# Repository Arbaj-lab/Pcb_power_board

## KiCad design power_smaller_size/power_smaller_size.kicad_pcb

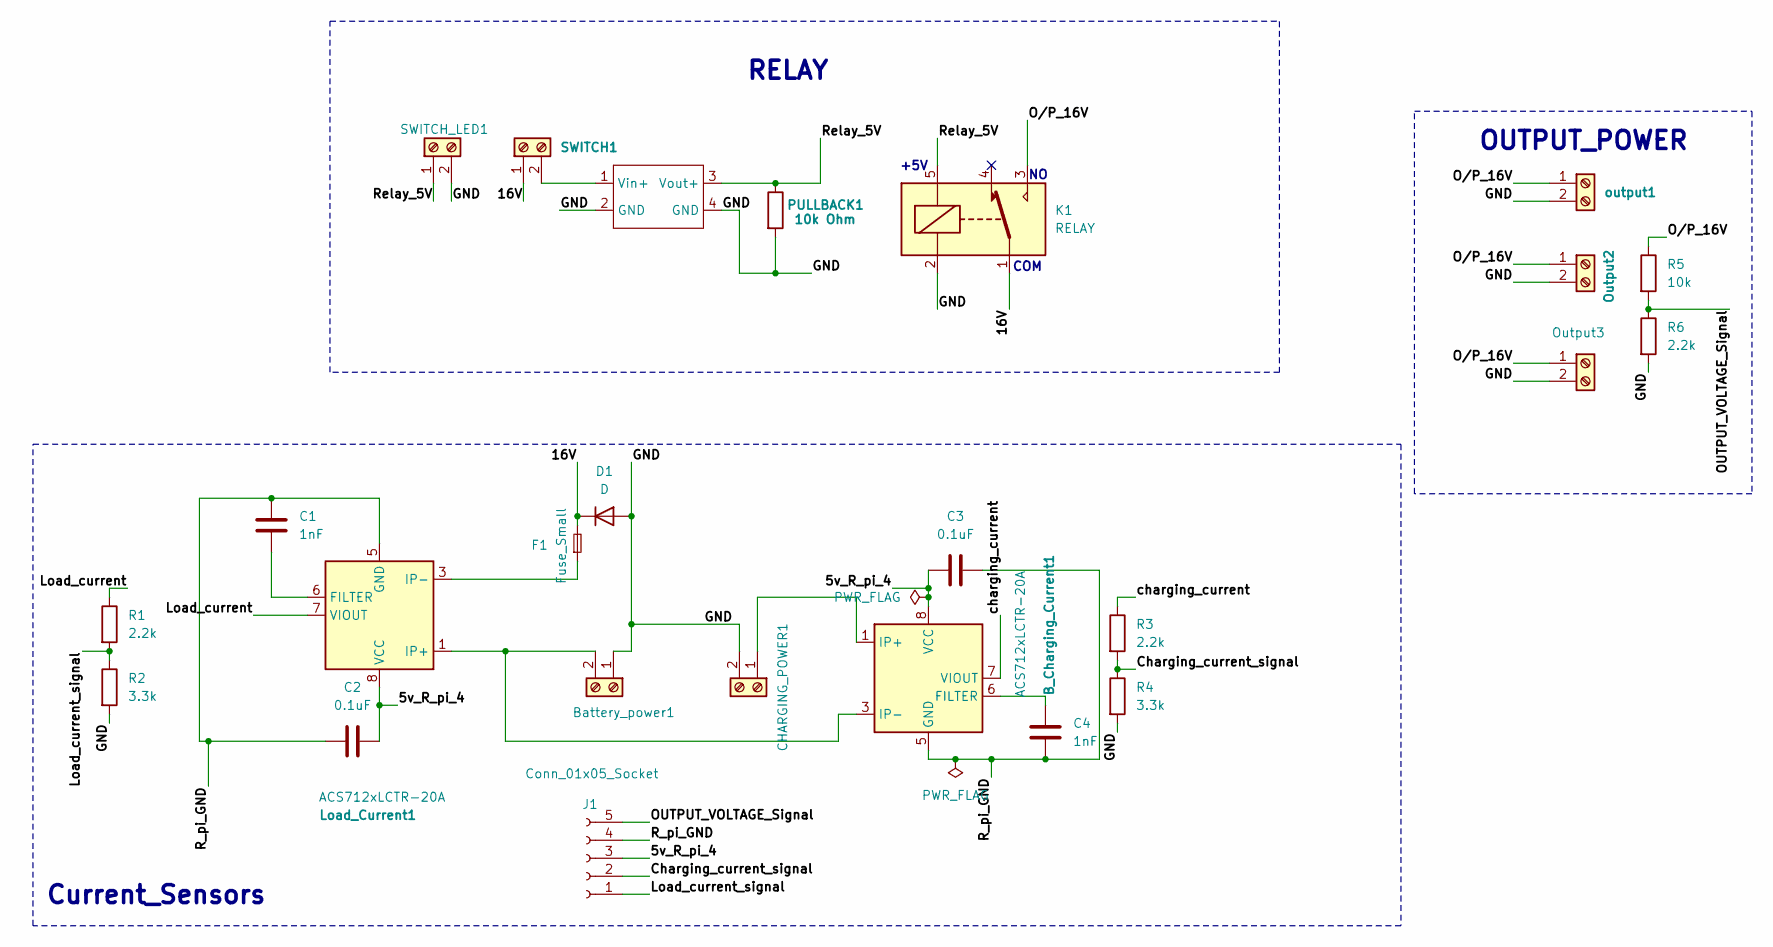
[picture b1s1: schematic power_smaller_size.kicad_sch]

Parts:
B_Charging_Current1: ACS712xLCTR-20A; SOIC-8_3.9x4.9mm_P1.27mm
Battery_power1: Screw_Terminal_01x02; TerminalBlock_bornier-2_P5.08mm
C1, C4: 1nF; C_1206_3216Metric
C2, C3: 0.1uF; C_1206_3216Metric
CHARGING_POWER1: Screw_Terminal_01x02; TerminalBlock_bornier-2_P5.08mm
D1: D; D_DO-27_P15.24mm_Horizontal
F1: Fuse_Small; Fuseholder_Cylinder-5x20mm_Schurter_0031_8201_Horizontal_Op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
J1: Conn_01x05_Socket; JST_XH_B5B-XH-AM_1x05_P2.50mm_Vertical
K1: RELAY; Relay_SPDT_SANYOU_SRD_Series_Form_C
Load_Current1: ACS712xLCTR-20A; SOIC-8_3.9x4.9mm_P1.27mm
Output2, Output3: Screw_Terminal_01x02; TerminalBlock_bornier-2_P5.08mm
PULLBACK1: 10k Ohm; R_1206_3216Metric_Pad1.30x1.75mm_HandSolder
R1, R3, R6: 2.2k; R_1206_3216Metric
R2, R4: 3.3k; R_1206_3216Metric
R5: 10k; R_1206_3216Metric_Pad1.30x1.75mm_HandSolder
SWITCH1: Screw_Terminal_01x02; TerminalBlock_bornier-2_P5.08mm
SWITCH_LED1: Screw_Terminal_01x02; TerminalBlock_bornier-2_P5.08mm
U1: Lm2596
output1: Screw_Terminal_01x02; TerminalBlock_bornier-2_P5.08mm

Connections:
/5v_R_pi_4: B_Charging_Current1.8 (VCC), C2.2, C3.1, J1.3, Load_Current1.8 (VCC)
/16V: D1.1 (K), F1.2, K1.1, SWITCH1.1
/Charging_current_signal: J1.2, R3.2, R4.1
/GND: Battery_power1.1, CHARGING_POWER1.2, D1.2 (A), K1.2, Output2.2, Output3.2, PULLBACK1.2, R2.2, R4.2, R6.2, SWITCH_LED1.2, U1.2 (GND), U1.4 (GND), output1.2
/Load_current: Load_Current1.7 (VIOUT), R1.1
/Load_current_signal: J1.1, R1.2, R2.1
/OUTPUT_VOLTAGE_Signal: J1.5, R5.2, R6.1
/O/P_16V: K1.3, Output2.1, Output3.1, R5.1, output1.1
/R_pi_GND: B_Charging_Current1.5 (GND), C1.1, C2.1, C3.2, C4.2, J1.4, Load_Current1.5 (GND)
/Relay_5V: K1.5, PULLBACK1.1, SWITCH_LED1.1, U1.3 (Vout+)
/charging_current: B_Charging_Current1.7 (VIOUT), R3.1
unnamed: B_Charging_Current1.6 (FILTER), C4.1
unnamed: B_Charging_Current1.3 (IP-), B_Charging_Current1.4 (IP-), Battery_power1.2, Load_Current1.1 (IP+), Load_Current1.2 (IP+)
unnamed: B_Charging_Current1.1 (IP+), B_Charging_Current1.2 (IP+), CHARGING_POWER1.1
unnamed: F1.1, Load_Current1.3 (IP-), Load_Current1.4 (IP-)
unnamed: C1.2, Load_Current1.6 (FILTER)
unnamed: SWITCH1.2, U1.1 (Vin+)

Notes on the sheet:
OUTPUT_POWER
RELAY
Current_Sensors
+5V
COM

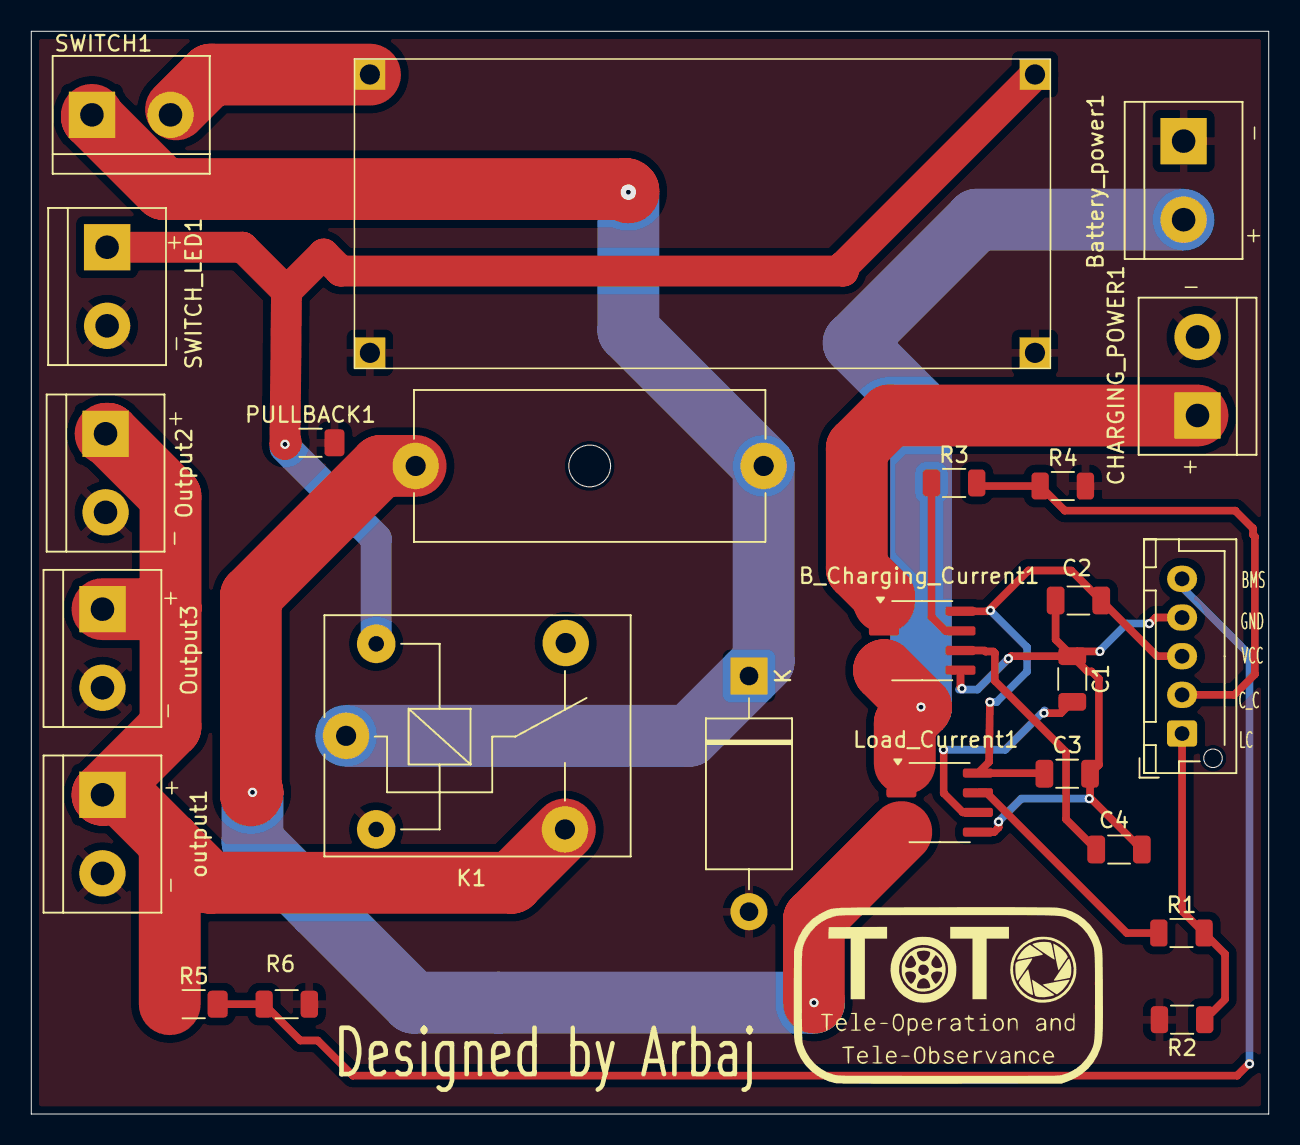
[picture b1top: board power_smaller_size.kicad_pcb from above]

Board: 2 copper layers, 80.0 x 70.0 mm, 25 parts (0 on the bottom side), 17 nets.
